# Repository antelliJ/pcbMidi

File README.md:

# musicDevice
A small MIDI capable keypad powered by an esp32-s3 for native USB compatibility

Components
- EC11 Rotary encoder
- SK6812 MINI-E neopixels
- Bourns Slide Potentiometers
- Kailh Choc Low-Profile Switches

The midi keys are built to be activated by capacitive touch based on the exposed copper on the PCB

I built this since I don't have a lot of space for an entire keyboard, so something simple can hopefully allow me to get something ready quickly if necessary
The lights on the back should also add a nice touch and some element of customizability

### Usage

Use [kmk firmware](https://github.com/KMKfw/kmk_firmware/tree/main) to get a circuitpython environment for the device to use the mechanical keyboard

MIDI configuration is dependent on the user's configuration

A test program `main.py` is included in the `\Code\` with the rest KMK repository alongside it to simplify organization

### 3D Casing
Included in the `\3dModels\` directory are another two directories, one (`\editable\`) with the original editable kicad file for the enclosure. The other (`\printable\`) is where print ready 3mf files for the case are provided

### Bill of Materials

| Ref     | Qty | Suggested Component             | Purpose | Supplier                                                   |
|---------|---|---------------------------------|-----------------------------------------------------------| -- |
| D1-D3   | 3 | SK6812 mini-e                   | Addressable LEDs behind keycaps| [JLCPCB](https://jlcpcb.com/partdetail/SK6812MINI-E/C5149201)  [Aliexpress](https://www.aliexpress.com/item/1005005193716172.html)                         |
| RV1-RV2 | 2 | Bourns PTA1543                  | Sliding potentiometer| [Mouser](https://www.mouser.ca/en/ProductDetail/Bourns/PTA1543-2015CIA103) [Aliexpress](https://www.aliexpress.com/item/1005003684684538.html)                                     |
| SW1-SW3 | 3 | Kailh Choc Low-Profile Switches | Nice mechanical keys| [Aliexpress](https://www.aliexpress.com/item/1005006120461718.html)                                      |
| SW4     | 1 | EC11 Rotary Encoder | knob             | [Aliexpress](https://www.aliexpress.com/item/1005007644083514.html) -- I Possess                                                      |
| U1      | 1 | Waveshare ESP32-S3-Zero         | Small form factor esp32, and is natively supported by KMK | [Aliexpress](https://www.aliexpress.com/item/1005012733231291.html)

### References
Based on the tutorial created by [KaiPerira](https://github.com/KaiPereira/midi-keypad)

Includes the [kmk firmware](https://github.com/KMKfw/kmk_firmware/tree/main) repository

#### Ai Declaration
Test circuitPython code was created by chatGPT

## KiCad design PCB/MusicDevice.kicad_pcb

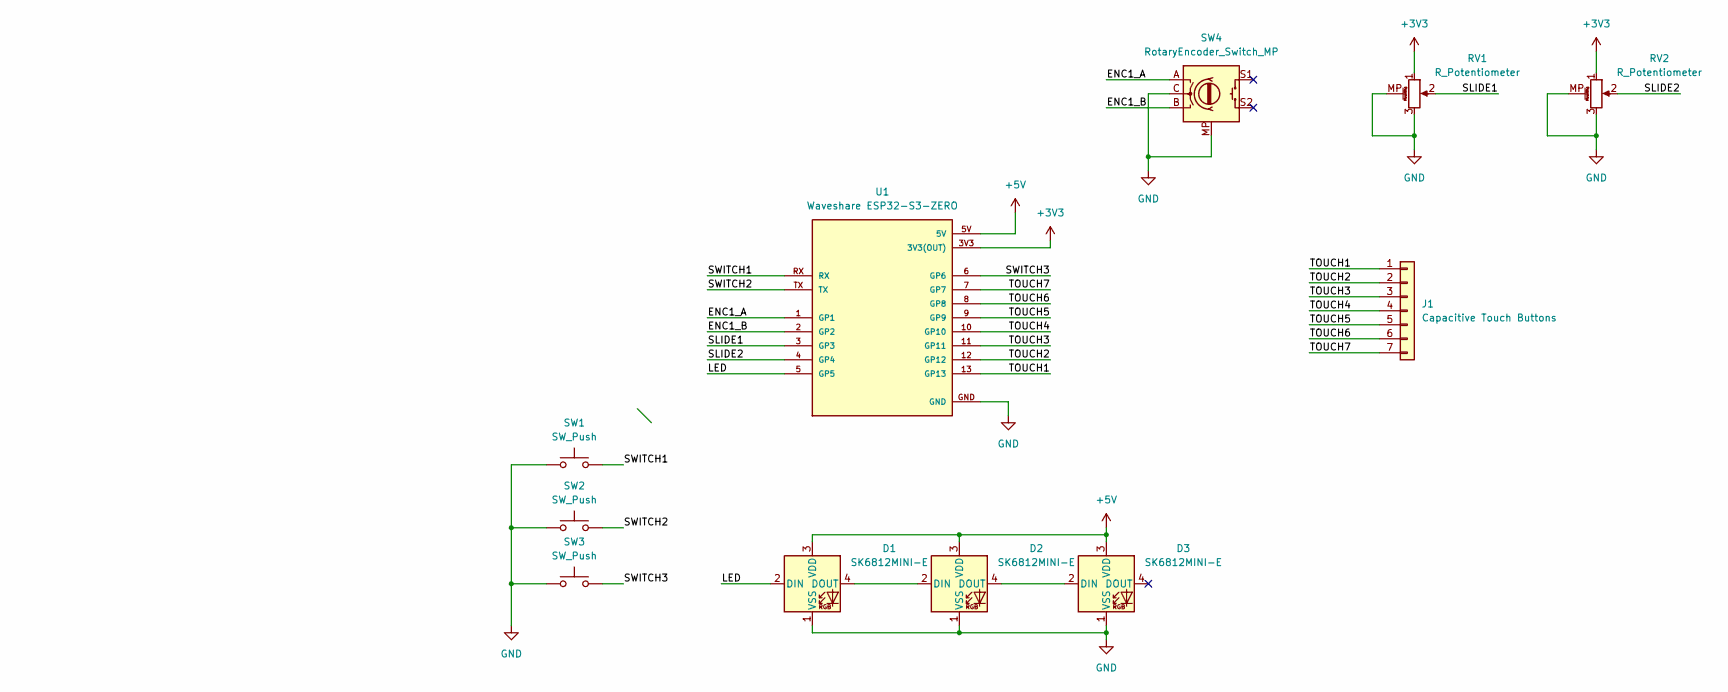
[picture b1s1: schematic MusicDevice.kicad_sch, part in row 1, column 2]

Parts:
D1, D2, D3: SK6812MINI-E; LED_SK6812MINI-E_3.2x2.8mm_P1.5mm_ReverseMount
J1: Capacitive Touch Buttons; Capacitive Keys
RV1, RV2: R_Potentiometer; Potentiometer_Bourns_PTA1543_Single_Slide
SW1, SW2, SW3: SW_Push; Kailh Choc Low-Profile Switches
SW4: RotaryEncoder_Switch_MP; RotaryEncoder_Alps_EC11E-Switch_Vertical_H20mm
U1: Waveshare ESP32-S3-ZERO; Waveshare ESP32-S3-Zero; PARTREV NA

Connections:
+3V3: RV1.1, RV2.1, U1.3V3 (3V3(OUT))
+5V: D1.3 (VDD), D2.3 (VDD), D3.3 (VDD), U1.5V
/ENC1_A: SW4.A, U1.1 (GP1)
/ENC1_B: SW4.B, U1.2 (GP2)
/LED: D1.2 (DIN), U1.5 (GP5)
/SLIDE1: RV1.2, U1.3 (GP3)
/SLIDE2: RV2.2, U1.4 (GP4)
/SWITCH1: SW1.2, U1.RX
/SWITCH2: SW2.2, U1.TX
/SWITCH3: SW3.2, U1.6 (GP6)
/TOUCH1: J1.1, U1.13 (GP13)
/TOUCH2: J1.2, U1.12 (GP12)
/TOUCH3: J1.3, U1.11 (GP11)
/TOUCH4: J1.4, U1.10 (GP10)
/TOUCH5: J1.5, U1.9 (GP9)
/TOUCH6: J1.6, U1.8 (GP8)
/TOUCH7: J1.7, U1.7 (GP7)
GND: D1.1 (VSS), D2.1 (VSS), D3.1 (VSS), RV1.3, RV1.MP (MountPin), RV2.3, RV2.MP (MountPin), SW1.1, SW2.1, SW3.1, SW4.C, SW4.MP, U1.GND
unnamed: D1.4 (DOUT), D2.2 (DIN)
unnamed: D2.4 (DOUT), D3.2 (DIN)

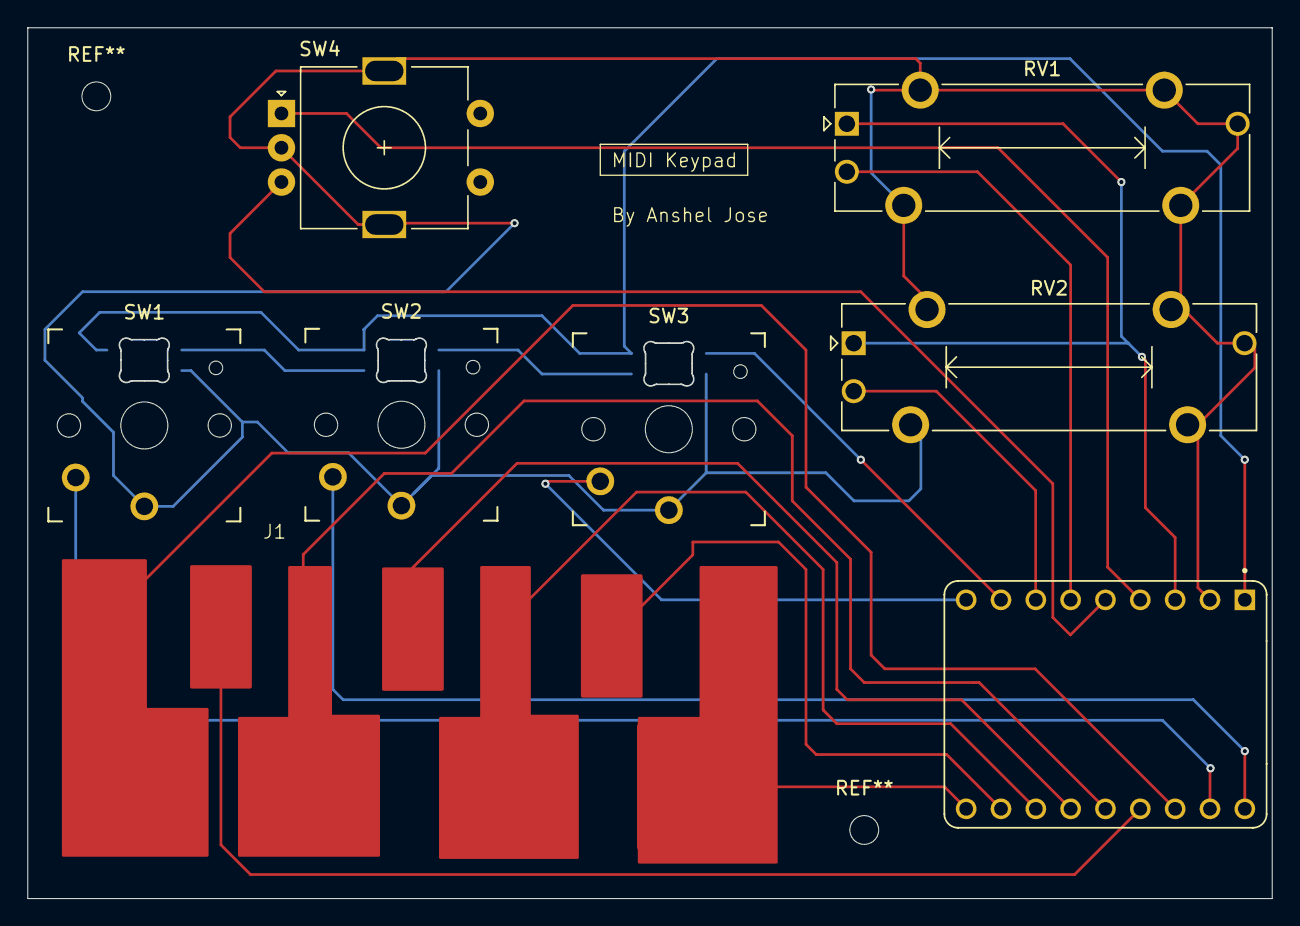
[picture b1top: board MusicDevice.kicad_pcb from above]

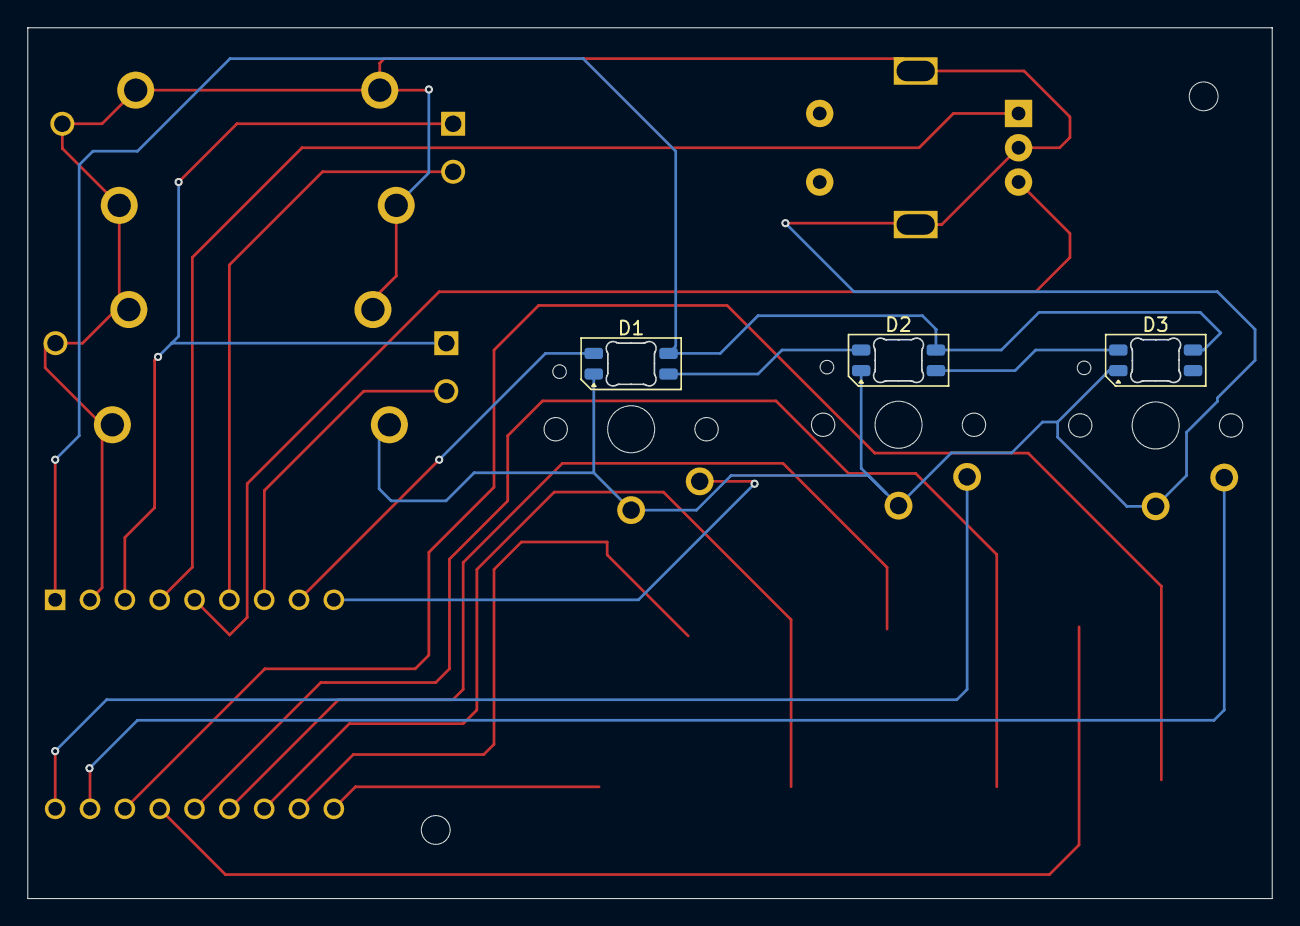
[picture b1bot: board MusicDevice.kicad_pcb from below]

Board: 2 copper layers, 90.8 x 63.5 mm, 11 parts (3 on the bottom side), 20 nets.

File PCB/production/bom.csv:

Designator,Footprint,Quantity,Value,Total Cost (USD),LCSC Part #,Description,Supplier,URL,Alternative
"D1, D2, D3",LED_SK6812MINI-E_3.2x2.8mm_P1.5mm_ReverseMount,3,SK6812MINI-E,2.55,,Addressable LEDs behind keycaps,AliExpress,https://www.aliexpress.com/item/1005005193716172.html,https://jlcpcb.com/partdetail/SK6812MINI-E/C5149201
J1,Capacitive Keys,1,Capacitive Touch Buttons,,,Capacitive touch buttons,,,
"RV1, RV2",Potentiometer_Bourns_PTA1543_Single_Slide,2,R_Potentiometer,2.54,,Sliding potentiometers,AliExpress,https://www.aliexpress.com/item/1005003684684538.html,https://www.mouser.ca/en/ProductDetail/Bourns/PTA1543-2015CIA103
"SW1, SW2, SW3",Kailh Choc Low-Profile Switches,3,SW_Push,9.21,,Mechanical keys; Kailh Choc low-profile switches,AliExpress,https://www.aliexpress.com/item/1005006120461718.html,
SW4,RotaryEncoder_Alps_EC11E-Switch_Vertical_H20mm,1,RotaryEncoder_Switch_MP,,,Rotary encoder knob/input; already owned,Already Owned,,
U1,Waveshare ESP32-S3-Zero,1,Waveshare ESP32-S3-ZERO,8.24,,Small-form-factor ESP32-S3 board; natively supported by KMK,AliExpress,https://www.aliexpress.com/item/1005012733231291.html,
,,,,,,,,,
,,,JLCPCB,2,,,,,
,,,,,,,,,
,,,TOTAL,24.54,,,,,

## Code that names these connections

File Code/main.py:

#This is the testing script that doesn't need kmk, 
# and can just be used independently to get output

# Basic setup, will need to consider:
# - the 3 mechanical buttons
# - the rotary encoder
# - the slide potentiometer
# - the RGB LED lights
# - capacitive touch input

print("Testing start")



import time
import board
import digitalio
import analogio
import rotaryio
import neopixel

# --------------------------------------------------
# Pin helper: board pin names vary between builds.
# --------------------------------------------------

def get_pin(*names):
    for name in names:
        if hasattr(board, name):
            return getattr(board, name)
    raise RuntimeError("Pin not found: " + ", ".join(names))


# --------------------------------------------------
# 1. Push buttons
# Schematic: buttons connect signal to GND.
# Therefore, use internal pull-ups.
# --------------------------------------------------

button_pins = {
    "SWITCH1": get_pin("RX", "IO44", "GPIO44"),
    "SWITCH2": get_pin("TX", "IO43", "GPIO43"),
    "SWITCH3": get_pin("IO6", "GPIO6", "GP6"),
}

buttons = {}

for name, pin in button_pins.items():
    btn = digitalio.DigitalInOut(pin)
    btn.direction = digitalio.Direction.INPUT
    btn.pull = digitalio.Pull.UP
    buttons[name] = btn


# --------------------------------------------------
# 2. Rotary encoder (A/B channels)
# --------------------------------------------------

encoder = rotaryio.IncrementalEncoder(
    get_pin("IO1", "GPIO1", "GP1"),
    get_pin("IO2", "GPIO2", "GP2"),
)

last_position = encoder.position


# --------------------------------------------------
# 3. Slide potentiometer
# SLIDE1 is the wiper / analog output.
# --------------------------------------------------

pot = analogio.AnalogIn(
    get_pin("IO3", "GPIO3", "GP3")
)


# --------------------------------------------------
# 4. SK6812 Mini-E addressable RGB LEDs
# --------------------------------------------------

pixels = neopixel.NeoPixel(
    get_pin("IO5", "GPIO5", "GP5"),
    3,
    brightness=0.15,
    auto_write=False,
)

# Startup test: red, green, blue, then off.
for color in [(255, 0, 0), (0, 255, 0), (0, 0, 255)]:
    pixels.fill(color)
    pixels.show()
    time.sleep(0.4)

pixels.fill((0, 0, 0))
pixels.show()


# --------------------------------------------------
# 5. Capacitive touch inputs
# ESP32-S3 touch-capable pins: GPIO7 through GPIO13.
# --------------------------------------------------

touch_pins = {
    "TOUCH1": ("IO13", "GPIO13", "GP13"),
    "TOUCH2": ("IO12", "GPIO12", "GP12"),
    "TOUCH3": ("IO11", "GPIO11", "GP11"),
    "TOUCH4": ("IO10", "GPIO10", "GP10"),
    "TOUCH5": ("IO9", "GPIO9", "GP9"),
    "TOUCH6": ("IO8", "GPIO8", "GP8"),
    "TOUCH7": ("IO7", "GPIO7", "GP7"),
}

touch_inputs = {}

try:
    import touchio

    for name, pin_names in touch_pins.items():
        try:
            touch_inputs[name] = touchio.TouchIn(
                get_pin(*pin_names)
            )
        except Exception as e:
            print(name, "unavailable:", repr(e))

except ImportError:
    print("touchio unavailable in this CircuitPython build.")


# --------------------------------------------------
# 6. Main test loop
# --------------------------------------------------

previous_buttons = {name: False for name in buttons}
previous_touches = {name: False for name in touch_inputs}

print("\nHardware test running.")
print("Press buttons, rotate encoder, move slider,")
print("touch electrodes, and watch the serial output.\n")

while True:
    # Push buttons
    for name, btn in buttons.items():
        pressed = not btn.value

        if pressed and not previous_buttons[name]:
            print(name, "PRESSED")

        previous_buttons[name] = pressed

    # Rotary encoder
    position = encoder.position

    if position != last_position:
        print("Encoder position:", position)
        last_position = position

    # Potentiometer: 0 to 65535
    print("Pot:", pot.value,
          "Voltage:", round(pot.value * 3.3 / 65535, 2), "V")

    # Capacitive touch: detect new touches
    for name, touch in touch_inputs.items():
        touched = touch.value

        if touched and not previous_touches[name]:
            print(name, "TOUCHED")

        previous_touches[name] = touched

    # Show encoder position on LEDs for a quick visual test.
    # A/B encoder direction should change the lit LED.
    led_index = position % 3
    pixels.fill((0, 0, 0))
    pixels[led_index] = (0, 40, 100)
    pixels.show()

    time.sleep(0.05)
